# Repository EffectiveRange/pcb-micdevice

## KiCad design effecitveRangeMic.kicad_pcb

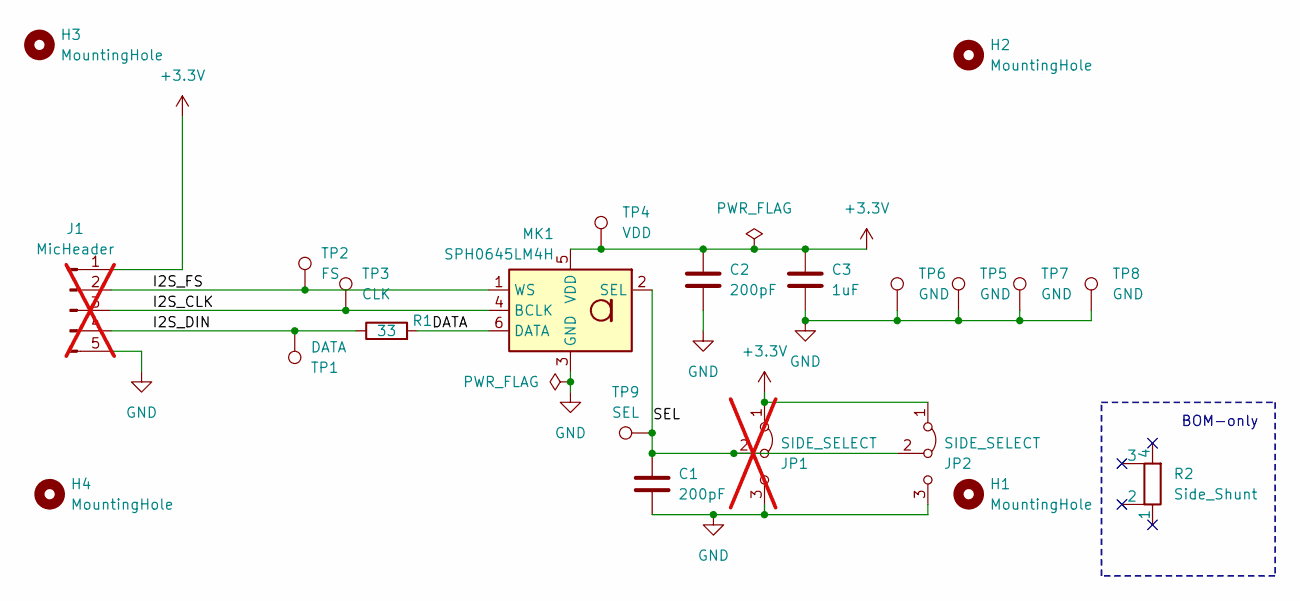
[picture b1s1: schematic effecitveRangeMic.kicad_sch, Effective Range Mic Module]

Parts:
C1, C2: 200pF; C_0603_1608Metric_Pad1.08x0.95mm_HandSolder; MPN GRM1885C2A201JA01D
C3: 1uF; C_0603_1608Metric_Pad1.08x0.95mm_HandSolder; MPN GRM188R61A105KA61D
H1, H2, H3, H4: MountingHole; MountingHole_2.7mm_M2.5_DIN965_Pad_TopBottom
J1: MicHeader; PinHeader_1x05_P2.54mm_Vertical_SMD_TH_Pin1Right; MPN 54201-S08-05ALF; not fitted
JP1: SIDE_SELECT; PinHeader_1x03_P2.54mm_Vertical_SMD_Pin1Right; MPN BG055-03A-1-0450-0530-0350-L-G; not fitted
JP2: SIDE_SELECT; SolderJumper-3_P2.0mm_Open_TrianglePad1.0x1.5mm; MPN BG055-03A-1-0450-0530-0350-L-G
MK1: SPH0645LM4H; Custom_Knowles_SPH0645LM4H-6_3.5x2.65mm; MPN SPH0645LM4H-B
R1: 33; R_0603_1608Metric_Pad0.98x0.95mm_HandSolder; MPN ERJ-3EKF33R0V
R2: Side_Shunt; MPN QPC02SXGN-RC
TP1: DATA; TestPoint_Pad_D1.0mm
TP2: FS; TestPoint_Pad_D1.0mm
TP3: CLK; TestPoint_Pad_D1.0mm
TP4: VDD; TestPoint_Pad_D1.0mm
TP5, TP6, TP7, TP8: GND; TestPoint_Pad_D1.0mm
TP9: SEL; TestPoint_Pad_D1.0mm

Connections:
+3.3V: C2.1, C3.1, J1.1, JP1.1 (A), JP2.1 (A), MK1.5 (VDD), TP4.1
/DATA: MK1.6 (DATA), R1.2
/I2S_CLK: J1.3, MK1.4 (BCLK), TP3.1
/I2S_DIN: J1.4, R1.1, TP1.1
/I2S_FS: J1.2, MK1.1 (WS), TP2.1
/SEL: C1.1, JP1.2 (C), JP2.2 (C), MK1.2 (SEL), TP9.1
GND: C1.2, C2.2, C3.2, J1.5, JP1.3 (B), JP2.3 (B), MK1.3 (GND), TP5.1, TP6.1, TP7.1, TP8.1

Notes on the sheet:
BOM-only

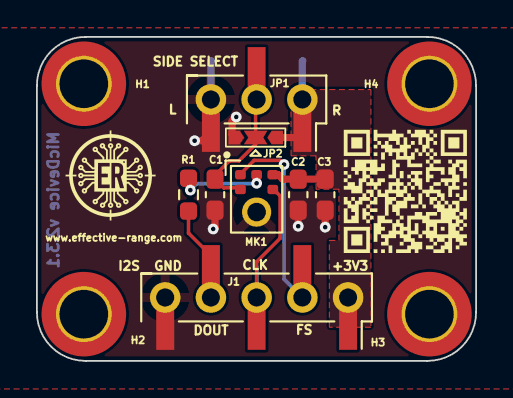
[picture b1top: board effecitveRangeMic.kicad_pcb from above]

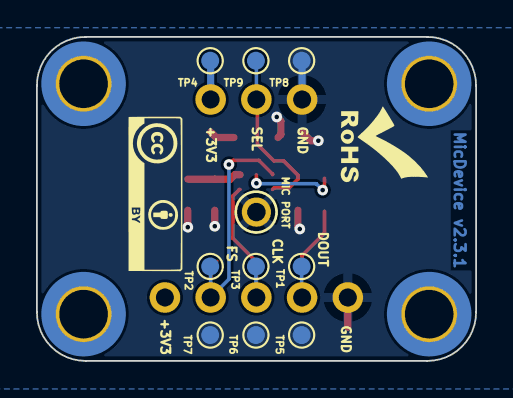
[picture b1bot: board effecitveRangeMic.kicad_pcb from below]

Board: 2 copper layers, 24.4 x 18.0 mm, 21 parts (9 on the bottom side), 7 nets.

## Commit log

2024-06-16 fix: drc check for font size
2024-06-16 Bumping release from 2.2.0 to 2.2.1
2024-06-16 fix: url in qr code
2024-06-16 Bumping release from 2.2.1 to 2.2.2
2024-07-24 fix: qr url, stencil
2024-07-24 Bumping release from 2.2.2 to 2.3.0
2024-10-06 fix: DRC error of pad clearance
2024-10-06 Bumping release from 2.3.0 to 2.3.1
2026-03-12 updated kicad file version

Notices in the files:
effecitveRangeMic.kicad_pcb:
License: All rights reserved
effecitveRangeMic.kicad_sch:
visit https://creativecommons.org/licenses/by/4.0
is licensed under CC BY 4.0. To view a copy of this license,
License: MicDevice© 2024 by Ferenc Nandor Janky & Attila Gombos
